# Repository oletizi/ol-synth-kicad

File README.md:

# Stuff

## TODO
- [X] Makefile to build stuff like Gerber and gcode
- [X] CLI for Kicad to export Gerber and Excellon files for PCB: https://docs.kicad.org/7.0/en/cli/cli.html

## GCODE Errors
- [ ] G04
- [ ] M6

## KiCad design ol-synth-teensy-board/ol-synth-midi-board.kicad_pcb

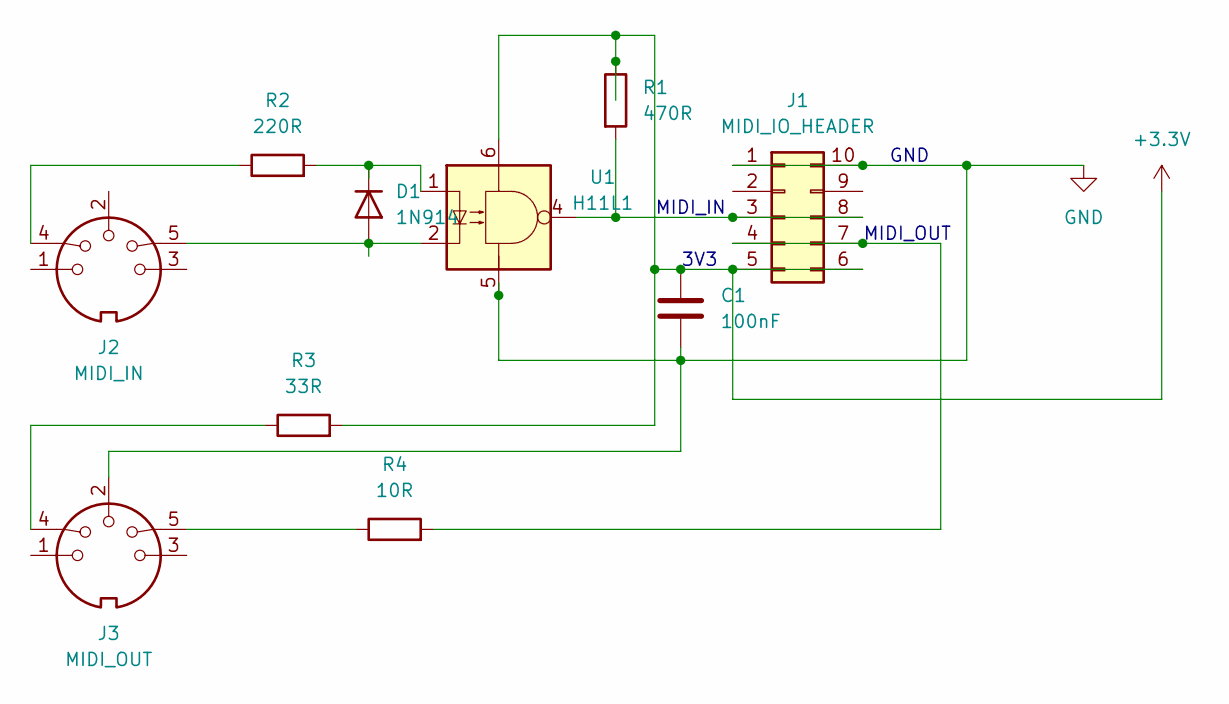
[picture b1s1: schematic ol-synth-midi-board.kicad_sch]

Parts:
C1: 100nF; CP_Axial_L10.0mm_D4.5mm_P15.00mm_Horizontal
D1: 1N914; D_DO-35_SOD27_P7.62mm_Horizontal
J1: MIDI_IO_HEADER; IDC-Header_2x05_P2.54mm_Vertical
J2: MIDI_IN; MIDI_DIN5
J3: MIDI_OUT; MIDI_DIN5
R1: 470R; R_Axial_DIN0207_L6.3mm_D2.5mm_P7.62mm_Horizontal
R2: 220R; R_Axial_DIN0207_L6.3mm_D2.5mm_P7.62mm_Horizontal
R3: 33R; R_Axial_DIN0207_L6.3mm_D2.5mm_P7.62mm_Horizontal
R4: 10R; R_Axial_DIN0207_L6.3mm_D2.5mm_P7.62mm_Horizontal
U1: H11L1; DIP-6_W7.62mm_Socket

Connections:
+3.3V: C1.1, J1.5, J1.6, R1.1, R3.2, U1.6
GND: C1.2, J1.1, J1.10, J3.2, U1.5
unnamed: D1.2 (A), J2.5, U1.2
unnamed: D1.1 (K), R2.2, U1.1
unnamed: J1.3, J1.8, R1.2, U1.4
unnamed: J1.4, J1.7, R4.2
unnamed: J2.4, R2.1
unnamed: J3.4, R3.1
unnamed: J3.5, R4.1

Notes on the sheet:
MIDI_IN
GND
3V3
MIDI_OUT

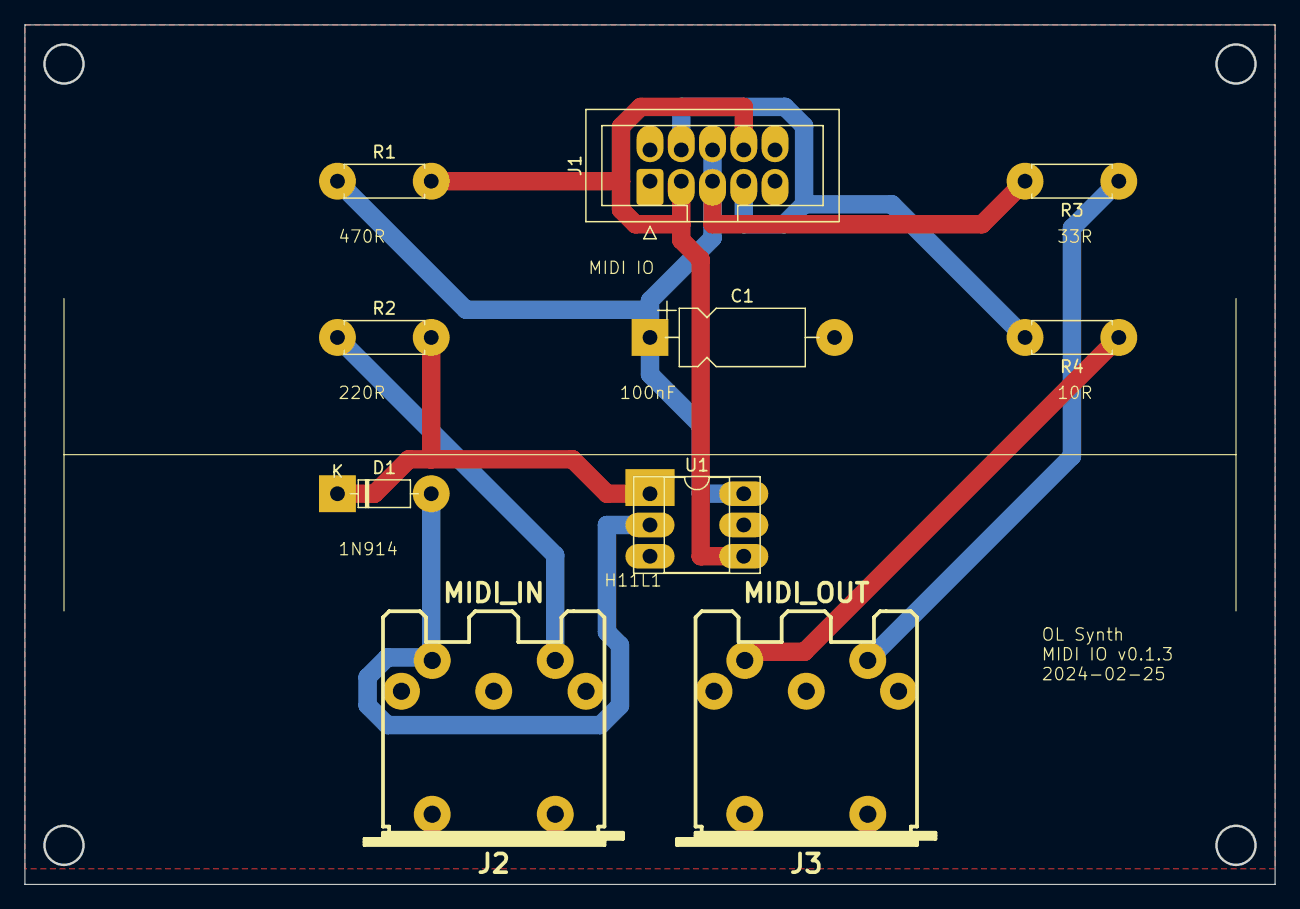
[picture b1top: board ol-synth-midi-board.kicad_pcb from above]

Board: 2 copper layers, 101.6 x 69.8 mm, 10 parts (0 on the bottom side), 9 nets.

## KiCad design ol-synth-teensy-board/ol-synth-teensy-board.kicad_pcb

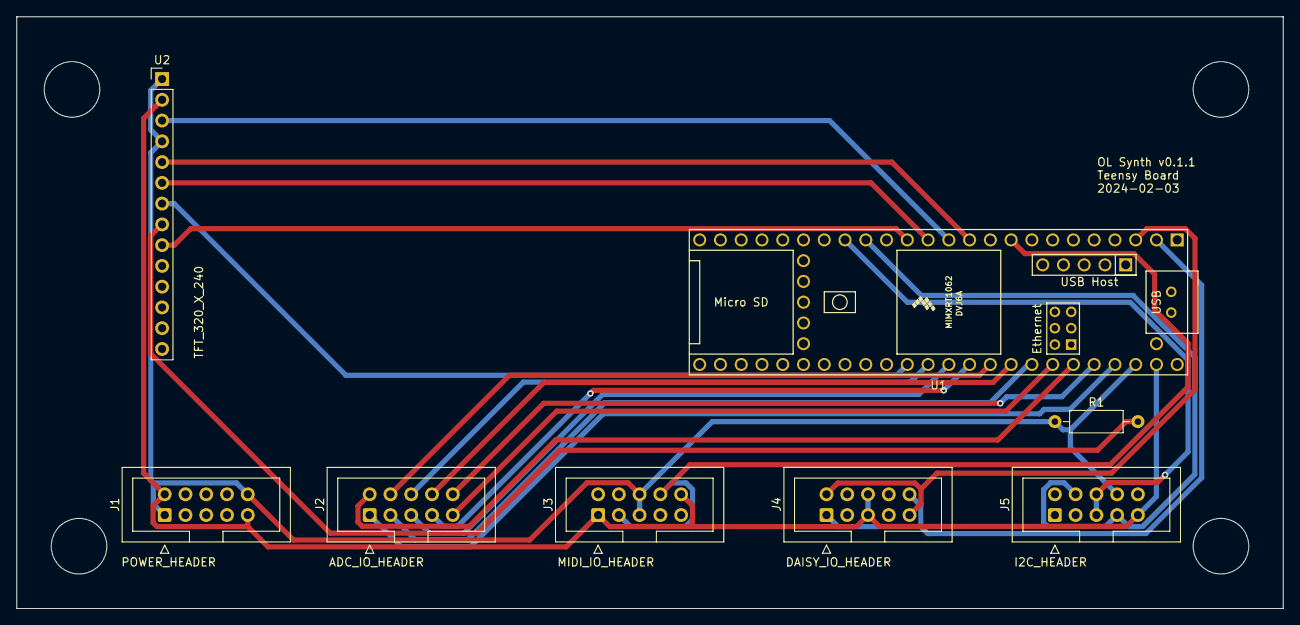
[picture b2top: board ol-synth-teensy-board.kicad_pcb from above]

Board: 2 copper layers, 154.9 x 72.4 mm, 8 parts (0 on the bottom side), 23 nets.

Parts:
J1: POWER_HEADER; IDC-Header_2x05_P2.54mm_Vertical
J2: ADC_IO_HEADER; IDC-Header_2x05_P2.54mm_Vertical
J3: MIDI_IO_HEADER; IDC-Header_2x05_P2.54mm_Vertical
J4: DAISY_IO_HEADER; IDC-Header_2x05_P2.54mm_Vertical
J5: I2C_HEADER; IDC-Header_2x05_P2.54mm_Vertical
R1: 100R; R_Axial_DIN0207_L6.3mm_D2.5mm_P10.16mm_Horizontal
U1: Teensy4.1; Teensy41
U2: TFT_320x240; PinHeader_1x14_P2.54mm_Vertical

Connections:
unnamed: J1.1, J1.10, J3.5, J3.6, J5.8, R1.1, U1.46 (3V3), U2.1 (VCC), U2.4 (RST)
unnamed: J1.2, J1.9, J3.1, J3.10, J4.5, J4.6, J5.9, U1.47 (GND), U2.2 (GND)
unnamed: J2.1, U1.45 (23_A9_CRX1_MCLK1)
unnamed: J2.2, U1.43 (21_A7_RX5_BCLK1)
unnamed: J2.3, U1.41 (19_A5_SCL)
unnamed: J2.4, U1.39 (17_A3_TX4_SDA1)
unnamed: J2.5, U1.37 (15_A1_RX3_SPDIF_IN)
unnamed: J2.6, U1.36 (14_A0_TX3_SPDIF_OUT)
unnamed: J2.7, U1.38 (16_A2_RX4_SCL1)
unnamed: J2.8, U1.40 (18_A4_SDA)
unnamed: J2.9, U1.42 (20_A6_TX5_LRCLK1)
unnamed: J2.10, U1.44 (22_A8_CTX1)
unnamed: J3.3, J3.8, U1.9 (7_RX2_OUT1A)
unnamed: J4.1, J4.10, U1.2 (0_RX1_CRX2_CS1)
unnamed: J4.2, J4.9, U1.3 (1_TX1_CTX2_MISO1)
unnamed: J5.4, J5.7, U1.16 (24_A10_TX6_SCL2)
unnamed: J5.5, J5.6, U1.17 (25_A11_RX6_SDA2)
unnamed: U1.11 (9_OUT1C), U2.5 (DC)
unnamed: U1.12 (10_CS_MQSR), U2.3 (CS)
unnamed: U1.13 (11_MOSI_CTX1), U2.6 (MOSI)
unnamed: U1.14 (12_MISO_MQSL), U2.9 (MISO)
unnamed: U1.35 (13_SCK_LED), U2.7 (SCK)
unnamed: R1.2, U2.8 (LED)

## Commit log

2024-02-27 init
2024-02-27 - start of a Makefile
2024-02-27 - more Makefile
2024-02-27 - Makefile target to export gerbers seems to work
2024-02-27 - fix for Makefile target to export gerbers
2024-02-27 - Makefile gcode target seems to be well formed
2024-02-27 - tweaks to pcb2gcode
2024-02-27 - added xgcode make target and a pattern-based target to convert gerbers to gcode
2024-02-28 - refactored boards into one per directory
2024-02-28 - switched gcode output to metric
2024-02-28 - turned off M06 output
2024-02-28 - gcode post-processing
2024-02-29 - found missing parameters for milldrill
2024-02-29 - fiddling with mirror axis - turned off X2 for Gerber exports (fixes warninggs from pcb2gcode
2024-03-03 - added mirror y axis to rear copper - added edge cuts gcode exports - added dxf extorts - added FreeCAD model of midi board
2024-03-03 - added step exports - added fusion-generated gcode for alignment holes
2024-03-03 - added track and zone exports from kicad 8
2024-03-03 - added fixture deep gcode from fusion
2024-03-03 - added fixture deep outline engraving gcode
2024-03-10 alignment-fixture
2024-03-11 - cleanup
2024-03-11 fixture gcode
2024-03-11 - removed autoleveling from pcb2gcode
2024-03-11 - removed nested parentheses
